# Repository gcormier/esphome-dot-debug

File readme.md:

# esphome-dot-debug
Debugging PCB for the project

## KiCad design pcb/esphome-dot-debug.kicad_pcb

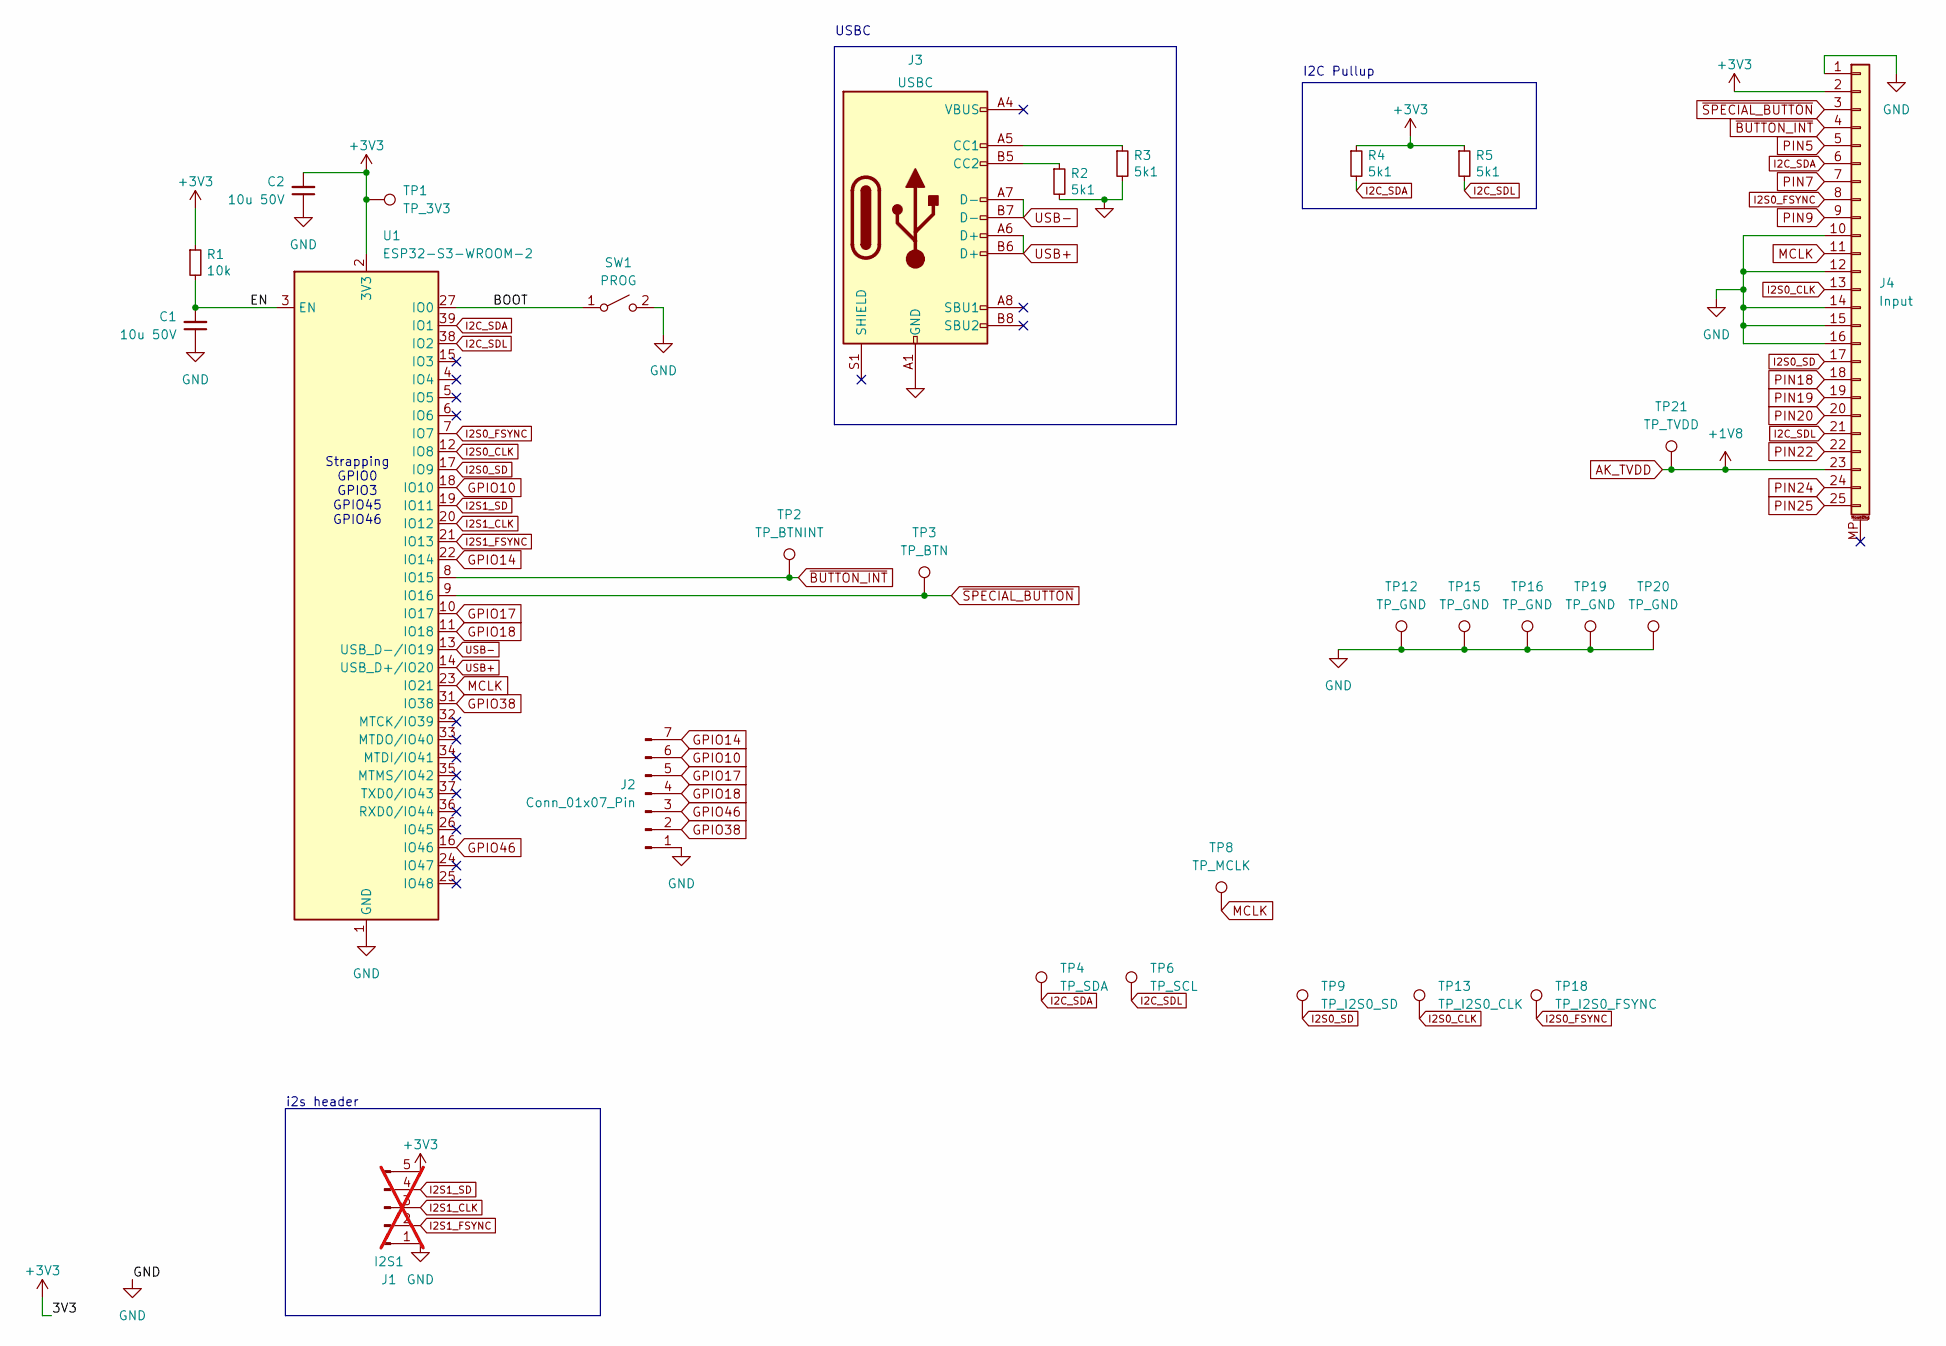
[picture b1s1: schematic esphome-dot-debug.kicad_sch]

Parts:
C1, C2: 10u 50V; C_1206_3216Metric; LCSC C13585
J1: I2S1; PinHeader_1x05_P2.54mm_Vertical; not fitted
J2: Conn_01x07_Pin; PinHeader_1x07_P2.54mm_Vertical
J3: USBC; USB_C_Receptacle_GCT_USB4105-xx-A_16P_TopMnt_Horizontal; LCSC C2765186
J4: Input; CONN_502598-2593_MOLEX; LCSC C3168400
R1: 10k; R_0402_1005Metric; LCSC C25744
R2, R3, R4, R5: 5k1; R_0402_1005Metric; LCSC C25905
SW1: PROG; SW_Push_1P1T_XKB_TS-1187A; LCSC C318884
TP1: TP_3V3; TestPoint_Loop_D2.60mm_Drill1.6mm_Beaded
TP2: TP_BTNINT; TestPoint_Loop_D2.60mm_Drill1.6mm_Beaded
TP3: TP_BTN; TestPoint_Loop_D2.60mm_Drill1.6mm_Beaded
TP4: TP_SDA; TestPoint_Loop_D2.60mm_Drill1.6mm_Beaded
TP6: TP_SCL; TestPoint_Loop_D2.60mm_Drill1.6mm_Beaded
TP8: TP_MCLK; TestPoint_Loop_D2.60mm_Drill1.6mm_Beaded
TP9: TP_I2S0_SD; TestPoint_Loop_D2.60mm_Drill1.6mm_Beaded
TP12, TP15, TP16, TP19, TP20: TP_GND; TestPoint_Loop_D2.60mm_Drill1.6mm_Beaded
TP13: TP_I2S0_CLK; TestPoint_Loop_D2.60mm_Drill1.6mm_Beaded
TP18: TP_I2S0_FSYNC; TestPoint_Loop_D2.60mm_Drill1.6mm_Beaded
TP21: TP_TVDD; TestPoint_Loop_D2.60mm_Drill1.6mm_Beaded
U1: ESP32-S3-WROOM-2

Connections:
+3V3: C2.2, J1.5, J4.2, R1.1, R4.1, R5.1, TP1.1, U1.2 (3V3)
/BOOT: SW1.1 (A), U1.27 (IO0)
/EN: C1.2, R1.2, U1.3 (EN)
AK_TVDD: J4.23, TP21.1
GND: C1.1, C2.1, J1.1, J2.1, J3.A1 (GND), J3.A12 (GND), J3.B1 (GND), J3.B12 (GND), J4.1, J4.10, J4.12, J4.14, J4.15, J4.16, R2.2, R3.2, SW1.2 (B), TP12.1, TP15.1, TP16.1, TP19.1, TP20.1, U1.1 (GND), U1.40 (GND), U1.41 (GND)
GPIO10: J2.6, U1.18 (IO10)
GPIO14: J2.7, U1.22 (IO14)
GPIO17: J2.5, U1.10 (IO17)
GPIO18: J2.4, U1.11 (IO18)
GPIO38: J2.2, U1.31 (IO38)
GPIO46: J2.3, U1.16 (IO46)
I2C_SDA: J4.6, R4.2, TP4.1, U1.39 (IO1)
I2C_SDL: J4.21, R5.2, TP6.1, U1.38 (IO2)
I2S0_CLK: J4.13, TP13.1, U1.12 (IO8)
I2S0_FSYNC: J4.8, TP18.1, U1.7 (IO7)
I2S0_SD: J4.17, TP9.1, U1.17 (IO9)
I2S1_CLK: J1.3, U1.20 (IO12)
I2S1_FSYNC: J1.2, U1.21 (IO13)
I2S1_SD: J1.4, U1.19 (IO11)
MCLK: J4.11, TP8.1, U1.23 (IO21)
unnamed: J3.A5 (CC1), R3.1
unnamed: J3.B5 (CC2), R2.1
PIN5: J4.5
PIN7: J4.7
PIN9: J4.9
PIN18: J4.18
PIN19: J4.19
PIN20: J4.20
PIN22: J4.22
PIN24: J4.24
PIN25: J4.25
USB+: J3.A6 (D+), J3.B6 (D+), U1.14 (USB_D+/IO20)
USB-: J3.A7 (D-), J3.B7 (D-), U1.13 (USB_D-/IO19)
~BUTTON_INT: J4.4, TP2.1, U1.8 (IO15)
~SPECIAL_BUTTON: J4.3, TP3.1, U1.9 (IO16)

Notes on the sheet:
Strapping GPIO0 GPIO3 GPIO45 GPIO46
i2s header
USBC
I2C Pullup

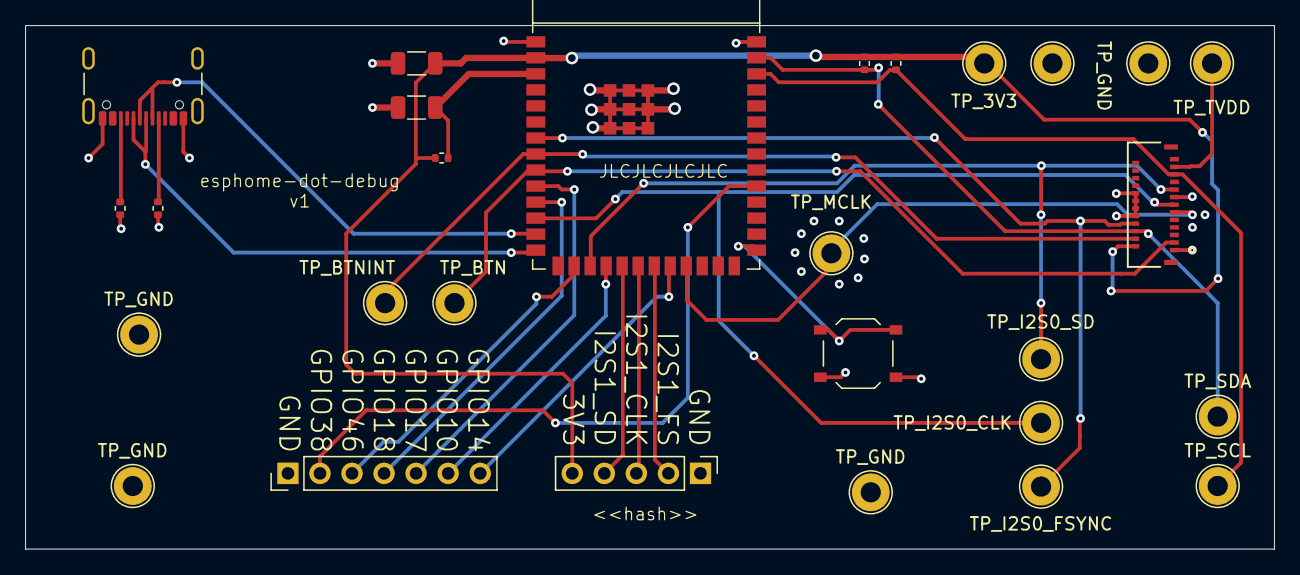
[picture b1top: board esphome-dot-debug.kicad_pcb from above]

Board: 4 copper layers, 99.0 x 41.5 mm, 28 parts (0 on the bottom side), 26 nets.

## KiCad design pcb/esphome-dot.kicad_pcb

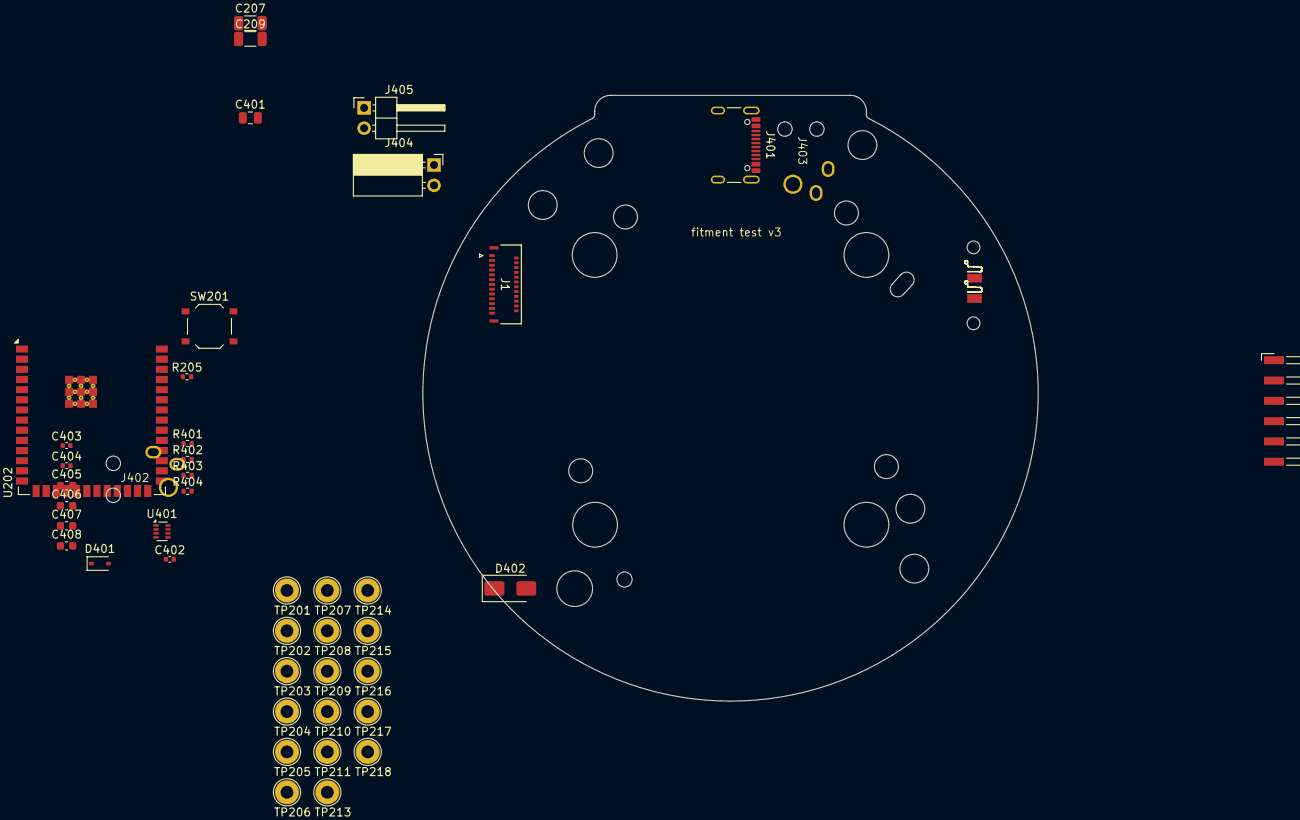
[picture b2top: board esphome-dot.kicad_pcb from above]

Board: 4 copper layers, 46 parts (0 on the bottom side), 27 nets, no tracks yet.

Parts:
C207, C209: 10u 50V; C_1206_3216Metric
C401: 10u; C_0805_2012Metric
C402, C403, C404: 100n; C_0402_1005Metric
C405: 27p; C_0603_1608Metric
C406, C407, C408: 10u; C_0603_1608Metric
D401: CUS05S40.H3F; D_SOD-323
D402: SMAJ22A; D_SMA
J1: Input; CONN_502598-2593_MOLEX
J5: SPK1; SF2212
J6: SPK2; SF2212
J201: eflashy32; Harwin_M20-89006xx_1x06_P2.54mm_Horizontal
J401: USBC; USB_C_Receptacle_GCT_USB4105-xx-A_16P_TopMnt_Horizontal
J402, J403: ADC-055B-9; BarrelJack_AdamTech_ADC-055B-9
J404: 20V; PinSocket_1x02_P2.54mm_Horizontal
J405: 20v; PinHeader_1x02_P2.54mm_Horizontal
R205: 10k; R_0402_1005Metric
R401, R402: 5k1; R_0402_1005Metric
R403: 68k; R_0402_1005Metric
R404: 22k; R_0402_1005Metric
SW201: RESET; SW_Push_1P1T_XKB_TS-1187A
TP201: TP_3V3; TestPoint_Loop_D2.60mm_Drill1.6mm_Beaded
TP202: TP_BTNINT; TestPoint_Loop_D2.60mm_Drill1.6mm_Beaded
TP203: TP_BTN; TestPoint_Loop_D2.60mm_Drill1.6mm_Beaded
TP204, TP205: TP_SDA; TestPoint_Loop_D2.60mm_Drill1.6mm_Beaded
TP206, TP207: TP_SCL; TestPoint_Loop_D2.60mm_Drill1.6mm_Beaded
TP208, TP209: TP_; TestPoint_Loop_D2.60mm_Drill1.6mm_Beaded
TP210: TP_MCLK; TestPoint_Loop_D2.60mm_Drill1.6mm_Beaded
TP211: TP_I2S0_SD; TestPoint_Loop_D2.60mm_Drill1.6mm_Beaded
TP213: TP_I2S1_SD; TestPoint_Loop_D2.60mm_Drill1.6mm_Beaded
TP214: TP_I2S0_CLK; TestPoint_Loop_D2.60mm_Drill1.6mm_Beaded
TP215: TP_I2S1_CLK; TestPoint_Loop_D2.60mm_Drill1.6mm_Beaded
TP216: TP_TVDD; TestPoint_Loop_D2.60mm_Drill1.6mm_Beaded
TP217: TP_I2S1_FSYNC; TestPoint_Loop_D2.60mm_Drill1.6mm_Beaded
TP218: TP_I2S0_FSYNC; TestPoint_Loop_D2.60mm_Drill1.6mm_Beaded
U202: ESP32-S3-WROOM-2
U401: TPS62932; SOT-583-8

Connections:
+3V3: C209.2, C405.1, C406.1, C407.1, C408.1, J201.4, R205.1, R403.2, TP201.1, U202.2 (3V3)
+20V: C401.1, C402.2, D401.1 (K), D402.1 (K), J402.1, J405.1, U401.3 (VIN)
/MCU/EN: C207.2, J201.5, R205.2, U202.3 (EN)
/MCU/GPIO0: J201.6, SW201.1 (A), U202.27 (IO0)
/Power/BST: C404.2, U401.6 (BST)
/Power/FB: C405.2, R403.1, R404.1, U401.8 (FB)
/Power/SW: C404.1, U401.5 (SW)
GND: C207.1, C209.1, C401.2, C402.1, C403.1, C406.2, C407.2, C408.2, D402.2 (A), J201.1, J401.A1 (GND), J401.A12 (GND), J401.B1 (GND), J401.B12 (GND), J402.2, J403.2, J404.2, J405.2, R401.2, R402.2, R404.2, SW201.2 (B), U202.4 (IO4), U202.6 (IO6), U401.1 (RT), U401.4 (GND)
I2C_SDA: TP204.1, TP205.1, U202.39 (IO1)
I2C_SDL: TP206.1, TP207.1, U202.38 (IO2)
I2S0_CLK: TP214.1, U202.12 (IO8)
I2S0_FSYNC: TP218.1, U202.7 (IO7)
I2S0_SD: TP211.1, U202.17 (IO9)
I2S1_CLK: TP215.1, U202.20 (IO12)
I2S1_FSYNC: TP217.1, U202.21 (IO13)
I2S1_SD: TP213.1, U202.19 (IO11)
MCLK: TP210.1, U202.5 (IO5)
unnamed: D401.2 (A), J401.A4 (VBUS), J401.A9 (VBUS), J401.B4 (VBUS), J401.B9 (VBUS)
unnamed: J401.A5 (CC1), R402.1
unnamed: J401.B5 (CC2), R401.1
unnamed: J403.1, J404.1
unnamed: U202.1 (GND), U202.40 (GND), U202.41 (GND)
unnamed: C403.2, U401.7 (SS)
USB+: J401.A6 (D+), J401.B6 (D+), U202.14 (USB_D+/IO20)
USB-: J401.A7 (D-), J401.B7 (D-), U202.13 (USB_D-/IO19)
~BUTTON_INT: TP202.1, U202.8 (IO15)
~SPECIAL_BUTTON: TP203.1, U202.9 (IO16)

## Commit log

2024-11-02 initial
2024-11-02 read
2024-11-03 action
2024-11-03 pcb-v1
